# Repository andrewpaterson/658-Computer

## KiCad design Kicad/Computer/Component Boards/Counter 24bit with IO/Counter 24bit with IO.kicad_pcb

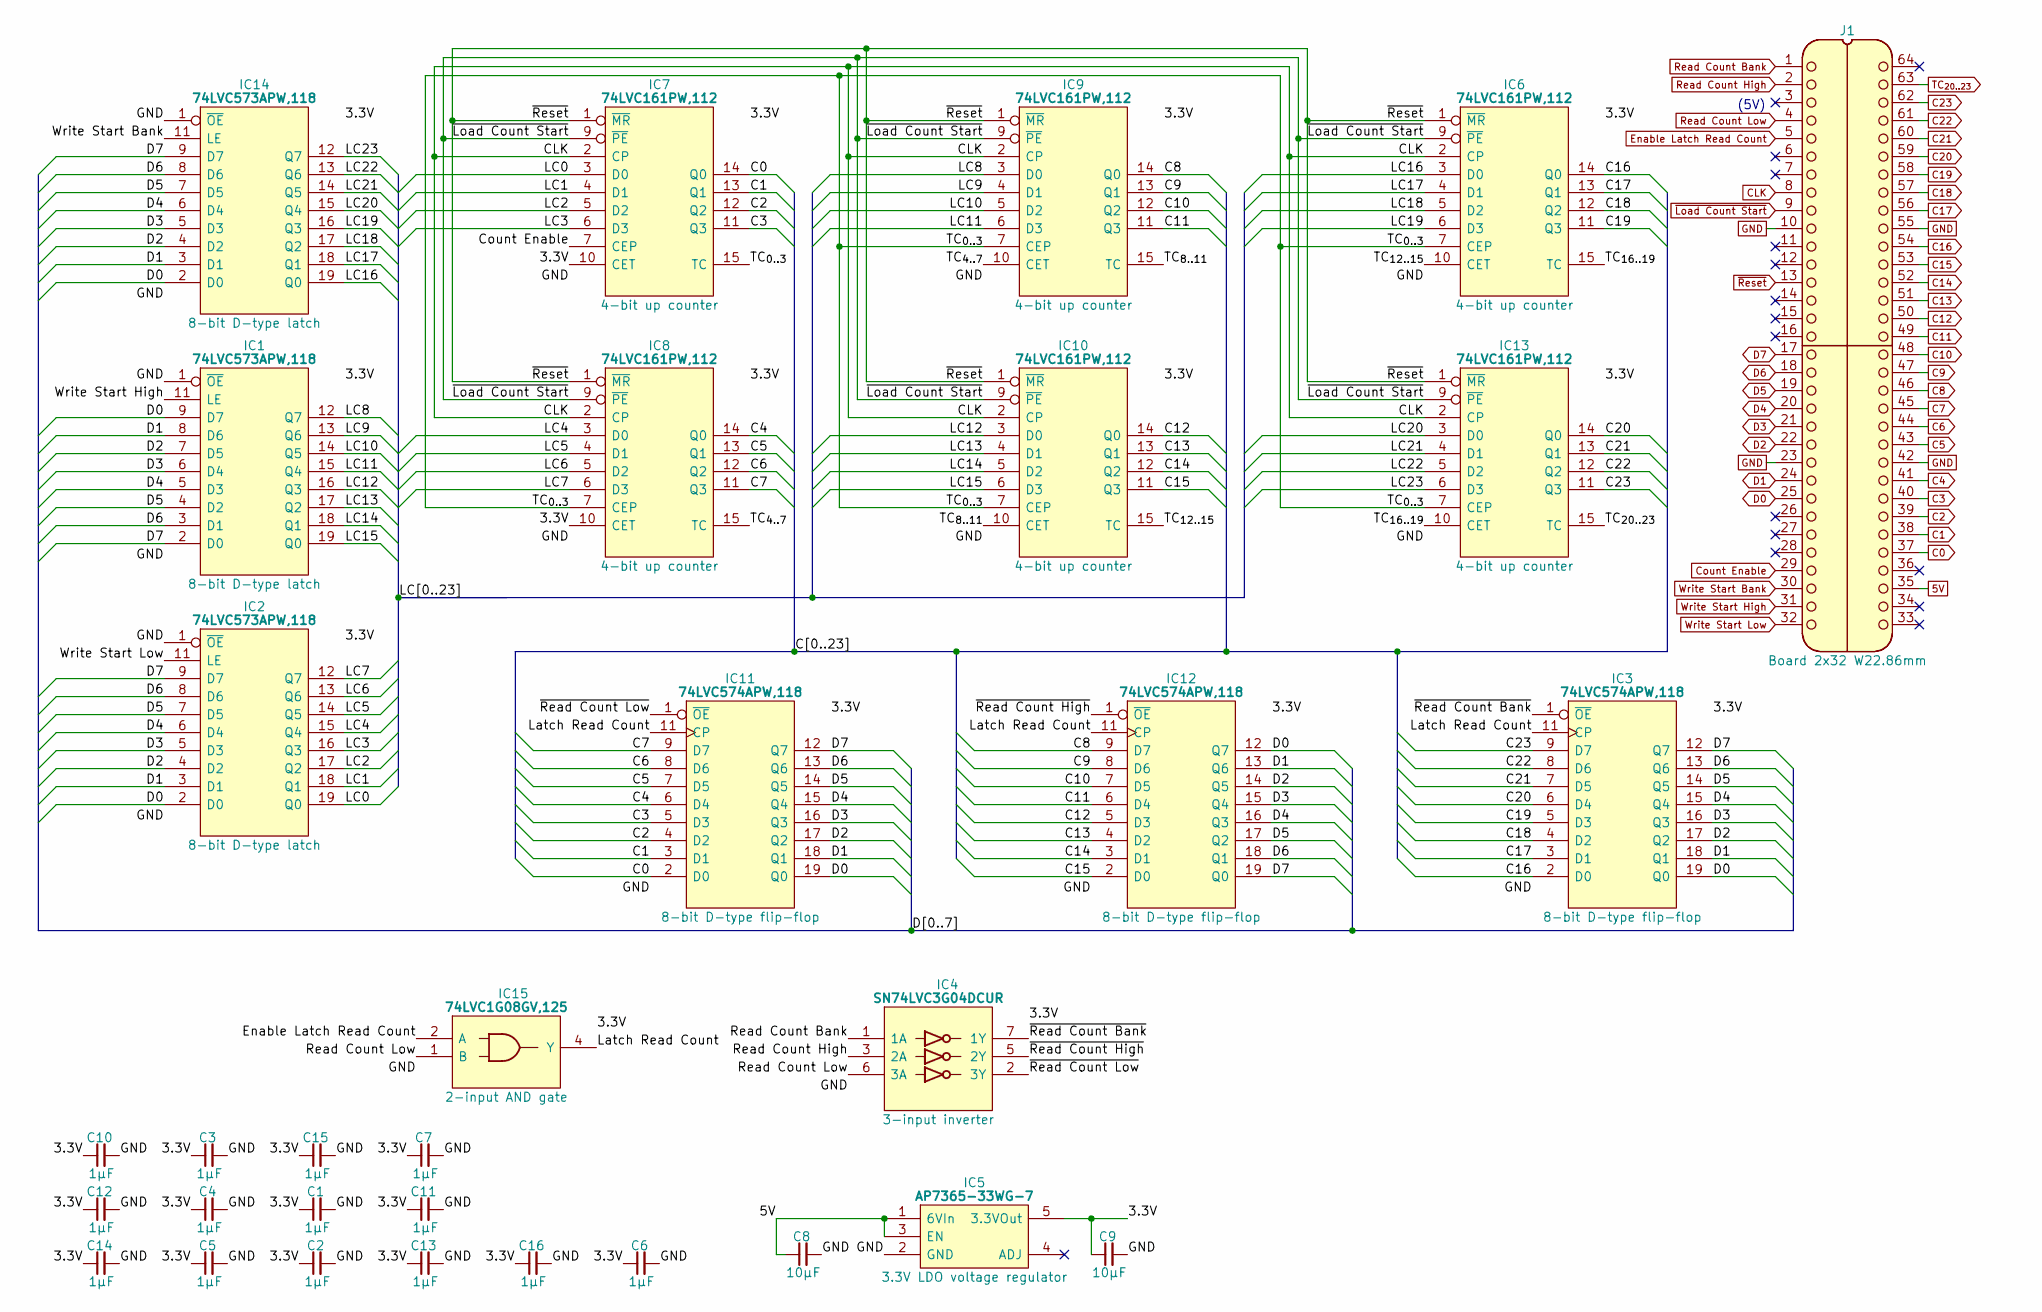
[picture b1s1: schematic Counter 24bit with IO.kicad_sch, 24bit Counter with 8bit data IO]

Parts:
C1, C2, C3, C4, C5, C6, C7, C10, C11, C12, C13, C14, C15, C16: 1μF; C_0805
C8, C9: 10µF; C_0805
IC1, IC2, IC14: 74LVC573APW,118; SOP65P640X110-20N; Mouser Part Number 771-74LVC573APW-T
IC3, IC11, IC12: 74LVC574APW,118; SOP65P640X110-20N; Manufacturer_Part_Number 74LVC574APW,118; Mouser Part Number 771-74LVC574APW-T
IC4: SN74LVC3G04DCUR; SOP50P310X90-8N; Manufacturer_Part_Number SN74LVC3G04DCUR; Mouser Part Number 595-SN74LVC3G04DCUR
IC5: AP7365-33WG-7; SOT95P285X130-5N; Manufacturer_Part_Number AP7365-33WG-7; Mouser Part Number 621-AP7365-33WG-7
IC6, IC7, IC8, IC9, IC10, IC13: 74LVC161PW,112; SOP65P640X110-16N; Mouser Part Number 771-LVC161PW112
IC15: 74LVC1G08GV,125; SOT95P275X110-5N; Manufacturer_Part_Number 74LVC1G08GV,125; Mouser Part Number 771-74LVC1G08GV
J1: Board 2x32 W22.86mm; DIP-64_Board_W22.86mm

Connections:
5V: C8.1, IC5.1 (6VIn), IC5.3 (EN), J1.35
/3.3V: C1.1, C2.1, C3.1, C4.1, C5.1, C6.1, C7.1, C9.1, C10.1, C11.1, C12.1, C13.1, C14.1, C15.1, C16.1, IC1.20 (3V), IC2.20 (3V), IC3.20 (3V), IC4.8 (3V), IC5.5 (3.3VOut), IC6.16 (3V), IC7.10 (CET), IC7.16 (3V), IC8.10 (CET), IC8.16 (3V), IC9.16 (3V), IC10.16 (3V), IC11.20 (3V), IC12.20 (3V), IC13.16 (3V), IC14.20 (3V), IC15.5 (3V)
/LC0: IC2.19 (Q0), IC7.3 (D0)
/LC1: IC2.18 (Q1), IC7.4 (D1)
/LC2: IC2.17 (Q2), IC7.5 (D2)
/LC3: IC2.16 (Q3), IC7.6 (D3)
/LC4: IC2.15 (Q4), IC8.3 (D0)
/LC5: IC2.14 (Q5), IC8.4 (D1)
/LC6: IC2.13 (Q6), IC8.5 (D2)
/LC7: IC2.12 (Q7), IC8.6 (D3)
/LC8: IC1.12 (Q7), IC9.3 (D0)
/LC9: IC1.13 (Q6), IC9.4 (D1)
/LC10: IC1.14 (Q5), IC9.5 (D2)
/LC11: IC1.15 (Q4), IC9.6 (D3)
/LC12: IC1.16 (Q3), IC10.3 (D0)
/LC13: IC1.17 (Q2), IC10.4 (D1)
/LC14: IC1.18 (Q1), IC10.5 (D2)
/LC15: IC1.19 (Q0), IC10.6 (D3)
/LC16: IC6.3 (D0), IC14.19 (Q0)
/LC17: IC6.4 (D1), IC14.18 (Q1)
/LC18: IC6.5 (D2), IC14.17 (Q2)
/LC19: IC6.6 (D3), IC14.16 (Q3)
/LC20: IC13.3 (D0), IC14.15 (Q4)
/LC21: IC13.4 (D1), IC14.14 (Q5)
/LC22: IC13.5 (D2), IC14.13 (Q6)
/LC23: IC13.6 (D3), IC14.12 (Q7)
/Latch Read Count: IC3.11 (CP), IC11.11 (CP), IC12.11 (CP), IC15.4 (Y)
/TC_{0..3}: IC6.7 (CEP), IC7.15 (TC), IC8.7 (CEP), IC9.7 (CEP), IC10.7 (CEP), IC13.7 (CEP)
/TC_{4..7}: IC8.15 (TC), IC9.10 (CET)
/TC_{8..11}: IC9.15 (TC), IC10.10 (CET)
/TC_{12..15}: IC6.10 (CET), IC10.15 (TC)
/TC_{16..19}: IC6.15 (TC), IC13.10 (CET)
/~Read Count Bank: IC3.1 (~OE), IC4.7 (1Y)
/~Read Count High: IC4.5 (2Y), IC12.1 (~OE)
/~Read Count Low: IC4.2 (3Y), IC11.1 (~OE)
C0: IC7.14 (Q0), IC11.2 (D0), J1.37
C1: IC7.13 (Q1), IC11.3 (D1), J1.38
C2: IC7.12 (Q2), IC11.4 (D2), J1.39
C3: IC7.11 (Q3), IC11.5 (D3), J1.40
C4: IC8.14 (Q0), IC11.6 (D4), J1.41
C5: IC8.13 (Q1), IC11.7 (D5), J1.43
C6: IC8.12 (Q2), IC11.8 (D6), J1.44
C7: IC8.11 (Q3), IC11.9 (D7), J1.45
C8: IC9.14 (Q0), IC12.9 (D7), J1.46
C9: IC9.13 (Q1), IC12.8 (D6), J1.47
C10: IC9.12 (Q2), IC12.7 (D5), J1.48
C11: IC9.11 (Q3), IC12.6 (D4), J1.49
C12: IC10.14 (Q0), IC12.5 (D3), J1.50
C13: IC10.13 (Q1), IC12.4 (D2), J1.51
C14: IC10.12 (Q2), IC12.3 (D1), J1.52
C15: IC10.11 (Q3), IC12.2 (D0), J1.53
C16: IC3.2 (D0), IC6.14 (Q0), J1.54
C17: IC3.3 (D1), IC6.13 (Q1), J1.56
C18: IC3.4 (D2), IC6.12 (Q2), J1.57
C19: IC3.5 (D3), IC6.11 (Q3), J1.58
C20: IC3.6 (D4), IC13.14 (Q0), J1.59
C21: IC3.7 (D5), IC13.13 (Q1), J1.60
C22: IC3.8 (D6), IC13.12 (Q2), J1.61
C23: IC3.9 (D7), IC13.11 (Q3), J1.62
CLK: IC6.2 (CP), IC7.2 (CP), IC8.2 (CP), IC9.2 (CP), IC10.2 (CP), IC13.2 (CP), J1.8
Count Enable: IC7.7 (CEP), J1.29
D0: IC1.9 (D7), IC2.2 (D0), IC3.19 (Q0), IC11.19 (Q0), IC12.12 (Q7), IC14.2 (D0), J1.25
D1: IC1.8 (D6), IC2.3 (D1), IC3.18 (Q1), IC11.18 (Q1), IC12.13 (Q6), IC14.3 (D1), J1.24
D2: IC1.7 (D5), IC2.4 (D2), IC3.17 (Q2), IC11.17 (Q2), IC12.14 (Q5), IC14.4 (D2), J1.22
D3: IC1.6 (D4), IC2.5 (D3), IC3.16 (Q3), IC11.16 (Q3), IC12.15 (Q4), IC14.5 (D3), J1.21
D4: IC1.5 (D3), IC2.6 (D4), IC3.15 (Q4), IC11.15 (Q4), IC12.16 (Q3), IC14.6 (D4), J1.20
D5: IC1.4 (D2), IC2.7 (D5), IC3.14 (Q5), IC11.14 (Q5), IC12.17 (Q2), IC14.7 (D5), J1.19
D6: IC1.3 (D1), IC2.8 (D6), IC3.13 (Q6), IC11.13 (Q6), IC12.18 (Q1), IC14.8 (D6), J1.18
D7: IC1.2 (D0), IC2.9 (D7), IC3.12 (Q7), IC11.12 (Q7), IC12.19 (Q0), IC14.9 (D7), J1.17
Enable Latch Read Count: IC15.2 (A), J1.5
GND: C1.2, C2.2, C3.2, C4.2, C5.2, C6.2, C7.2, C8.2, C9.2, C10.2, C11.2, C12.2, C13.2, C14.2, C15.2, C16.2, IC1.1 (~OE), IC1.10 (GND), IC2.1 (~OE), IC2.10 (GND), IC3.10 (GND), IC4.4 (GND), IC5.2 (GND), IC6.8 (GND), IC7.8 (GND), IC8.8 (GND), IC9.8 (GND), IC10.8 (GND), IC11.10 (GND), IC12.10 (GND), IC13.8 (GND), IC14.1 (~OE), IC14.10 (GND), IC15.3 (GND), J1.10, J1.23, J1.42, J1.55
Read Count Bank: IC4.1 (1A), J1.1
Read Count High: IC4.3 (2A), J1.2
Read Count Low: IC4.6 (3A), IC15.1 (B), J1.4
TC_{20..23}: IC13.15 (TC), J1.63
Write Start Bank: IC14.11 (LE), J1.30
Write Start High: IC1.11 (LE), J1.31
Write Start Low: IC2.11 (LE), J1.32
~Load Count Start: IC6.9 (~PE), IC7.9 (~PE), IC8.9 (~PE), IC9.9 (~PE), IC10.9 (~PE), IC13.9 (~PE), J1.9
~Reset: IC6.1 (~MR), IC7.1 (~MR), IC8.1 (~MR), IC9.1 (~MR), IC10.1 (~MR), IC13.1 (~MR), J1.13

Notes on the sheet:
(5V)

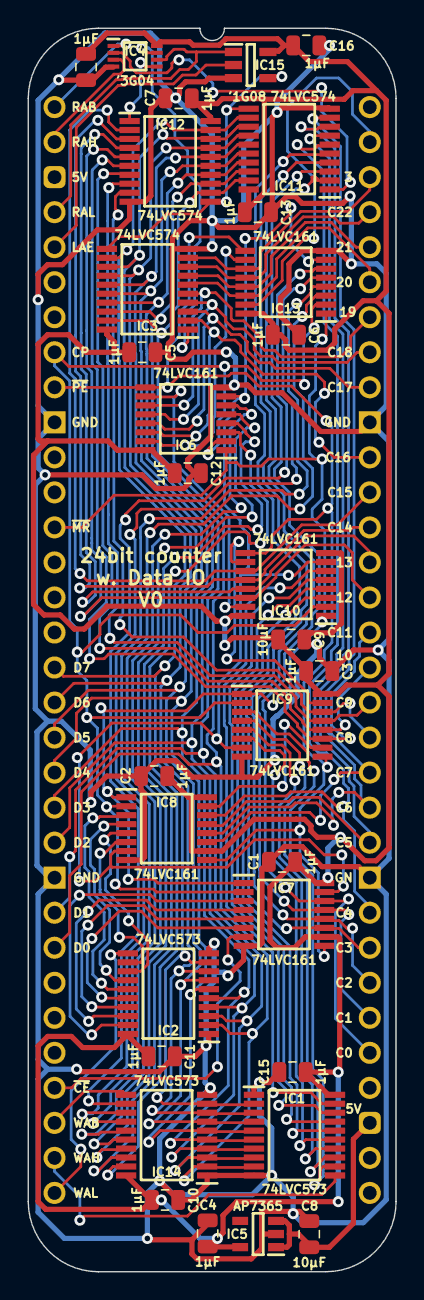
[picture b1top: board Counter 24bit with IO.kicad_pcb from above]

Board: 2 copper layers, 26.7 x 90.2 mm, 32 parts (0 on the bottom side), 80 nets.

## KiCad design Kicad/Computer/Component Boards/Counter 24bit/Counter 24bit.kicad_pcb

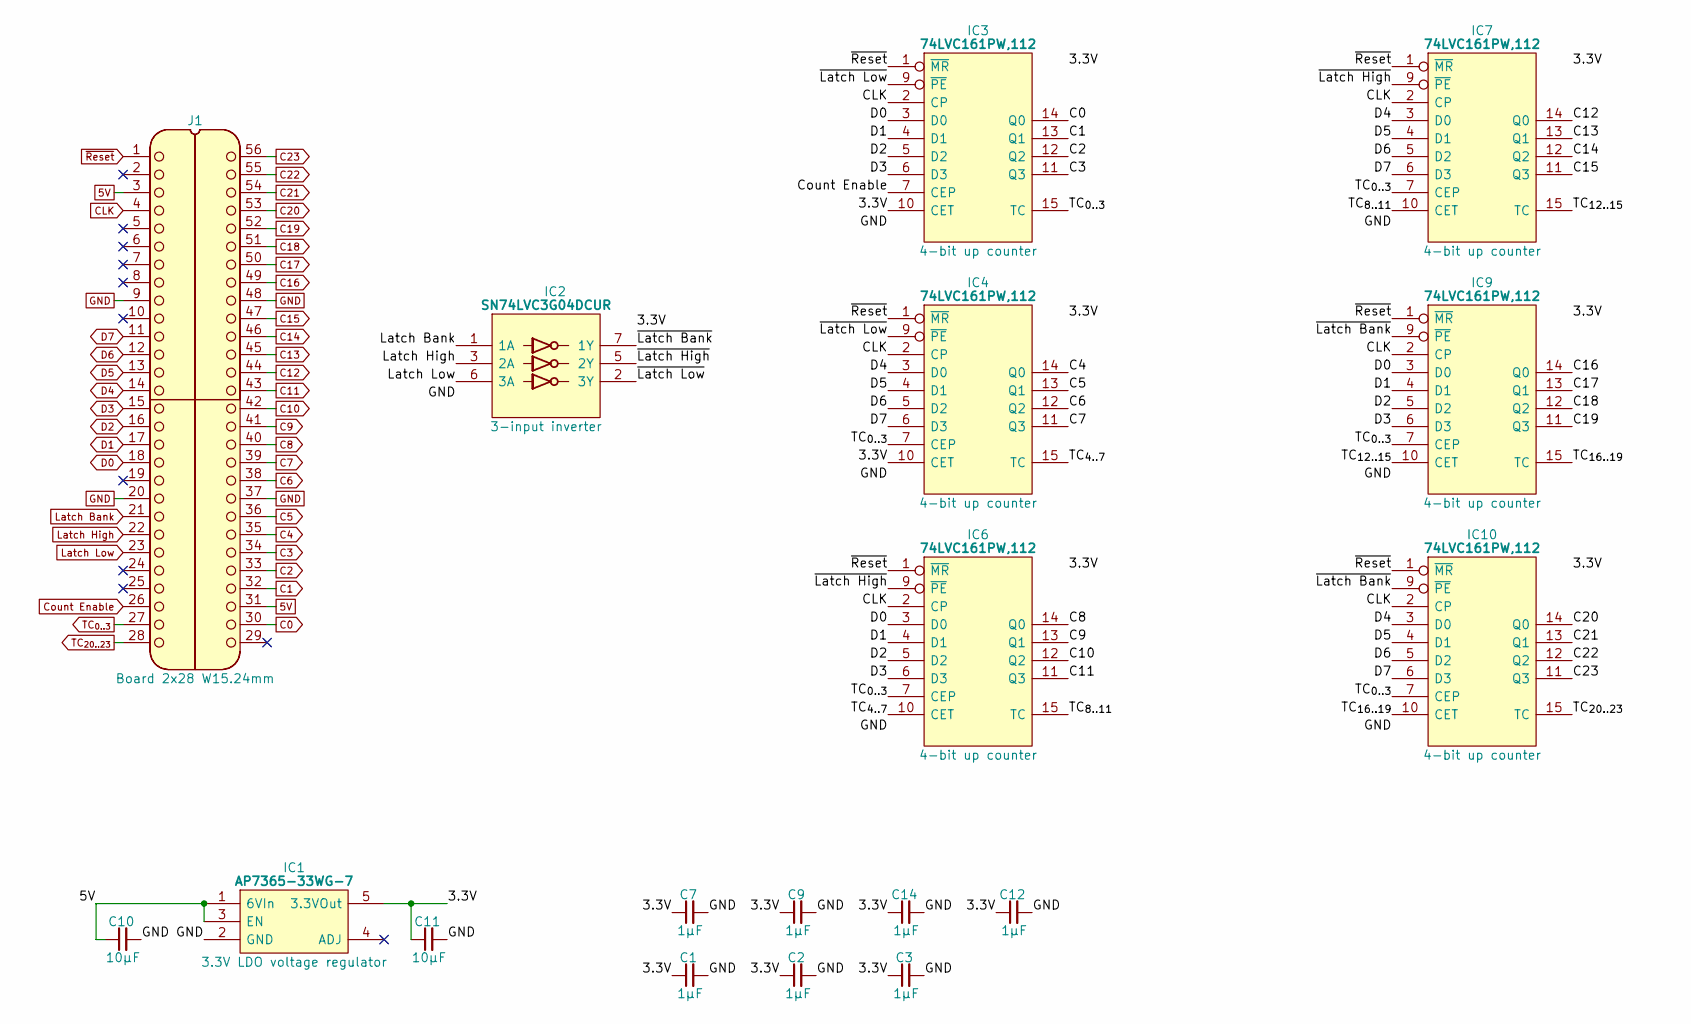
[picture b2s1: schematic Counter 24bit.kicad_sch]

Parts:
C1, C2, C3, C7, C9, C12, C14: 1μF; C_0805
C10, C11: 10µF; C_0805
IC1: AP7365-33WG-7; SOT95P285X130-5N; Manufacturer_Part_Number AP7365-33WG-7; Mouser Part Number 621-AP7365-33WG-7
IC2: SN74LVC3G04DCUR; SOP50P310X90-8N; Manufacturer_Part_Number SN74LVC3G04DCUR; Mouser Part Number 595-SN74LVC3G04DCUR
IC3, IC4, IC6, IC7, IC9, IC10: 74LVC161PW,112; SOP65P640X110-16N; Mouser Part Number 771-LVC161PW112
J1: Board 2x28 W15.24mm; DIP-56_Board_W15.24mm

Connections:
5V: C10.1, IC1.1 (6VIn), IC1.3 (EN), J1.3, J1.31
/3.3V: C1.1, C2.1, C3.1, C7.1, C9.1, C11.1, C12.1, C14.1, IC1.5 (3.3VOut), IC2.8 (3V), IC3.10 (CET), IC3.16 (3V), IC4.10 (CET), IC4.16 (3V), IC6.16 (3V), IC7.16 (3V), IC9.16 (3V), IC10.16 (3V)
/TC_{4..7}: IC4.15 (TC), IC6.10 (CET)
/TC_{8..11}: IC6.15 (TC), IC7.10 (CET)
/TC_{12..15}: IC7.15 (TC), IC9.10 (CET)
/TC_{16..19}: IC9.15 (TC), IC10.10 (CET)
/~Latch Bank: IC2.7 (1Y), IC9.9 (~PE), IC10.9 (~PE)
/~Latch High: IC2.5 (2Y), IC6.9 (~PE), IC7.9 (~PE)
/~Latch Low: IC2.2 (3Y), IC3.9 (~PE), IC4.9 (~PE)
C0: IC3.14 (Q0), J1.30
C1: IC3.13 (Q1), J1.32
C2: IC3.12 (Q2), J1.33
C3: IC3.11 (Q3), J1.34
C4: IC4.14 (Q0), J1.35
C5: IC4.13 (Q1), J1.36
C6: IC4.12 (Q2), J1.38
C7: IC4.11 (Q3), J1.39
C8: IC6.14 (Q0), J1.40
C9: IC6.13 (Q1), J1.41
C10: IC6.12 (Q2), J1.42
C11: IC6.11 (Q3), J1.43
C12: IC7.14 (Q0), J1.44
C13: IC7.13 (Q1), J1.45
C14: IC7.12 (Q2), J1.46
C15: IC7.11 (Q3), J1.47
C16: IC9.14 (Q0), J1.49
C17: IC9.13 (Q1), J1.50
C18: IC9.12 (Q2), J1.51
C19: IC9.11 (Q3), J1.52
C20: IC10.14 (Q0), J1.53
C21: IC10.13 (Q1), J1.54
C22: IC10.12 (Q2), J1.55
C23: IC10.11 (Q3), J1.56
CLK: IC3.2 (CP), IC4.2 (CP), IC6.2 (CP), IC7.2 (CP), IC9.2 (CP), IC10.2 (CP), J1.4
Count Enable: IC3.7 (CEP), J1.26
D0: IC3.3 (D0), IC6.3 (D0), IC9.3 (D0), J1.18
D1: IC3.4 (D1), IC6.4 (D1), IC9.4 (D1), J1.17
D2: IC3.5 (D2), IC6.5 (D2), IC9.5 (D2), J1.16
D3: IC3.6 (D3), IC6.6 (D3), IC9.6 (D3), J1.15
D4: IC4.3 (D0), IC7.3 (D0), IC10.3 (D0), J1.14
D5: IC4.4 (D1), IC7.4 (D1), IC10.4 (D1), J1.13
D6: IC4.5 (D2), IC7.5 (D2), IC10.5 (D2), J1.12
D7: IC4.6 (D3), IC7.6 (D3), IC10.6 (D3), J1.11
GND: C1.2, C2.2, C3.2, C7.2, C9.2, C10.2, C11.2, C12.2, C14.2, IC1.2 (GND), IC2.4 (GND), IC3.8 (GND), IC4.8 (GND), IC6.8 (GND), IC7.8 (GND), IC9.8 (GND), IC10.8 (GND), J1.9, J1.20, J1.37, J1.48
Latch Bank: IC2.1 (1A), J1.21
Latch High: IC2.3 (2A), J1.22
Latch Low: IC2.6 (3A), J1.23
TC_{0..3}: IC3.15 (TC), IC4.7 (CEP), IC6.7 (CEP), IC7.7 (CEP), IC9.7 (CEP), IC10.7 (CEP), J1.27
TC_{20..23}: IC10.15 (TC), J1.28
~Reset: IC3.1 (~MR), IC4.1 (~MR), IC6.1 (~MR), IC7.1 (~MR), IC9.1 (~MR), IC10.1 (~MR), J1.1

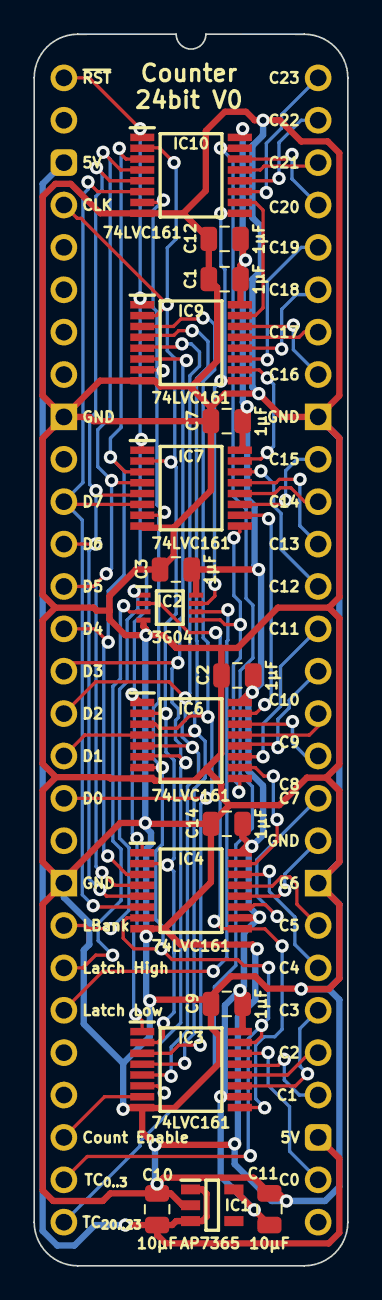
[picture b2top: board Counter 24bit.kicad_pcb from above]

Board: 2 copper layers, 18.8 x 73.8 mm, 18 parts (0 on the bottom side), 50 nets.

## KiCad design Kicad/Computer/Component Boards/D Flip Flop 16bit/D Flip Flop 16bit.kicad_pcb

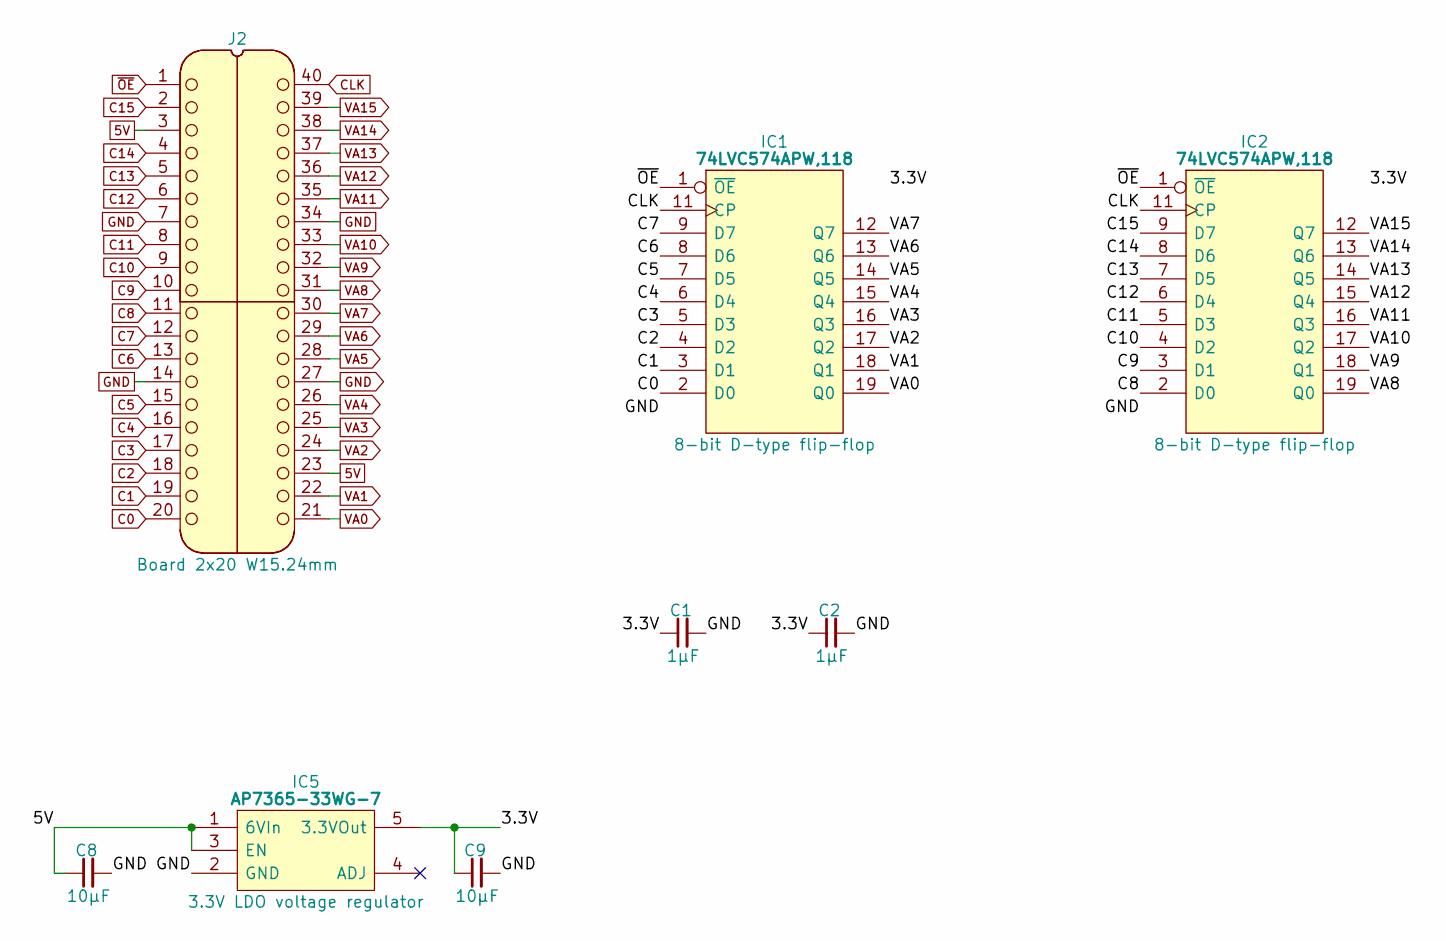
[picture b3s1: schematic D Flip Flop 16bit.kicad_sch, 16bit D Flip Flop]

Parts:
C1, C2: 1μF; C_0805
C8, C9: 10µF; C_0805
IC1, IC2: 74LVC574APW,118; SOP65P640X110-20N; Manufacturer_Part_Number 74LVC574APW,118; Mouser Part Number 771-74LVC574APW-T
IC5: AP7365-33WG-7; SOT95P285X130-5N; Manufacturer_Part_Number AP7365-33WG-7; Mouser Part Number 621-AP7365-33WG-7
J2: Board 2x20 W15.24mm; DIP-40_Board_W15.24mm

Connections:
5V: C8.1, IC5.1 (6VIn), IC5.3 (EN), J2.3, J2.23
/3.3V: C1.1, C2.1, C9.1, IC1.20 (3V), IC2.20 (3V), IC5.5 (3.3VOut)
C0: IC1.2 (D0), J2.20
C1: IC1.3 (D1), J2.19
C2: IC1.4 (D2), J2.18
C3: IC1.5 (D3), J2.17
C4: IC1.6 (D4), J2.16
C5: IC1.7 (D5), J2.15
C6: IC1.8 (D6), J2.13
C7: IC1.9 (D7), J2.12
C8: IC2.2 (D0), J2.11
C9: IC2.3 (D1), J2.10
C10: IC2.4 (D2), J2.9
C11: IC2.5 (D3), J2.8
C12: IC2.6 (D4), J2.6
C13: IC2.7 (D5), J2.5
C14: IC2.8 (D6), J2.4
C15: IC2.9 (D7), J2.2
CLK: IC1.11 (CP), IC2.11 (CP), J2.40
GND: C1.2, C2.2, C8.2, C9.2, IC1.10 (GND), IC2.10 (GND), IC5.2 (GND), J2.7, J2.14, J2.27, J2.34
VA0: IC1.19 (Q0), J2.21
VA1: IC1.18 (Q1), J2.22
VA2: IC1.17 (Q2), J2.24
VA3: IC1.16 (Q3), J2.25
VA4: IC1.15 (Q4), J2.26
VA5: IC1.14 (Q5), J2.28
VA6: IC1.13 (Q6), J2.29
VA7: IC1.12 (Q7), J2.30
VA8: IC2.19 (Q0), J2.31
VA9: IC2.18 (Q1), J2.32
VA10: IC2.17 (Q2), J2.33
VA11: IC2.16 (Q3), J2.35
VA12: IC2.15 (Q4), J2.36
VA13: IC2.14 (Q5), J2.37
VA14: IC2.13 (Q6), J2.38
VA15: IC2.12 (Q7), J2.39
~OE: IC1.1 (~OE), IC2.1 (~OE), J2.1

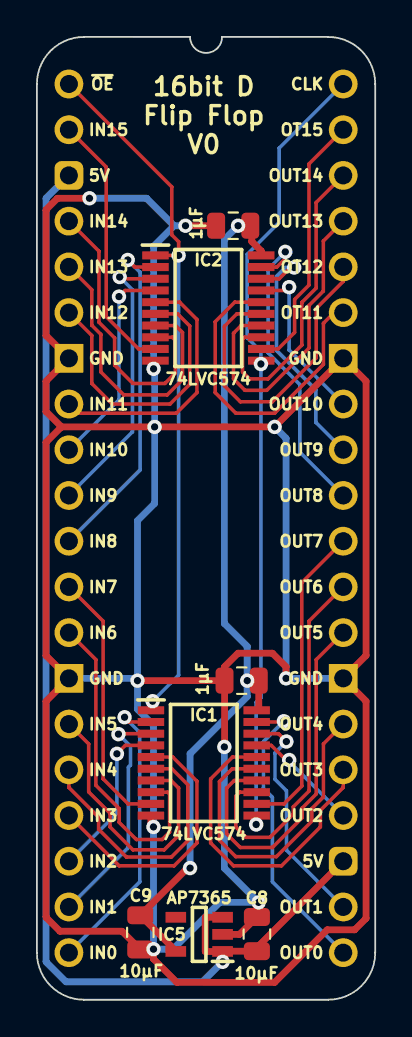
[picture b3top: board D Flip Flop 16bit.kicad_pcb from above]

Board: 2 copper layers, 18.8 x 53.5 mm, 8 parts (0 on the bottom side), 37 nets.

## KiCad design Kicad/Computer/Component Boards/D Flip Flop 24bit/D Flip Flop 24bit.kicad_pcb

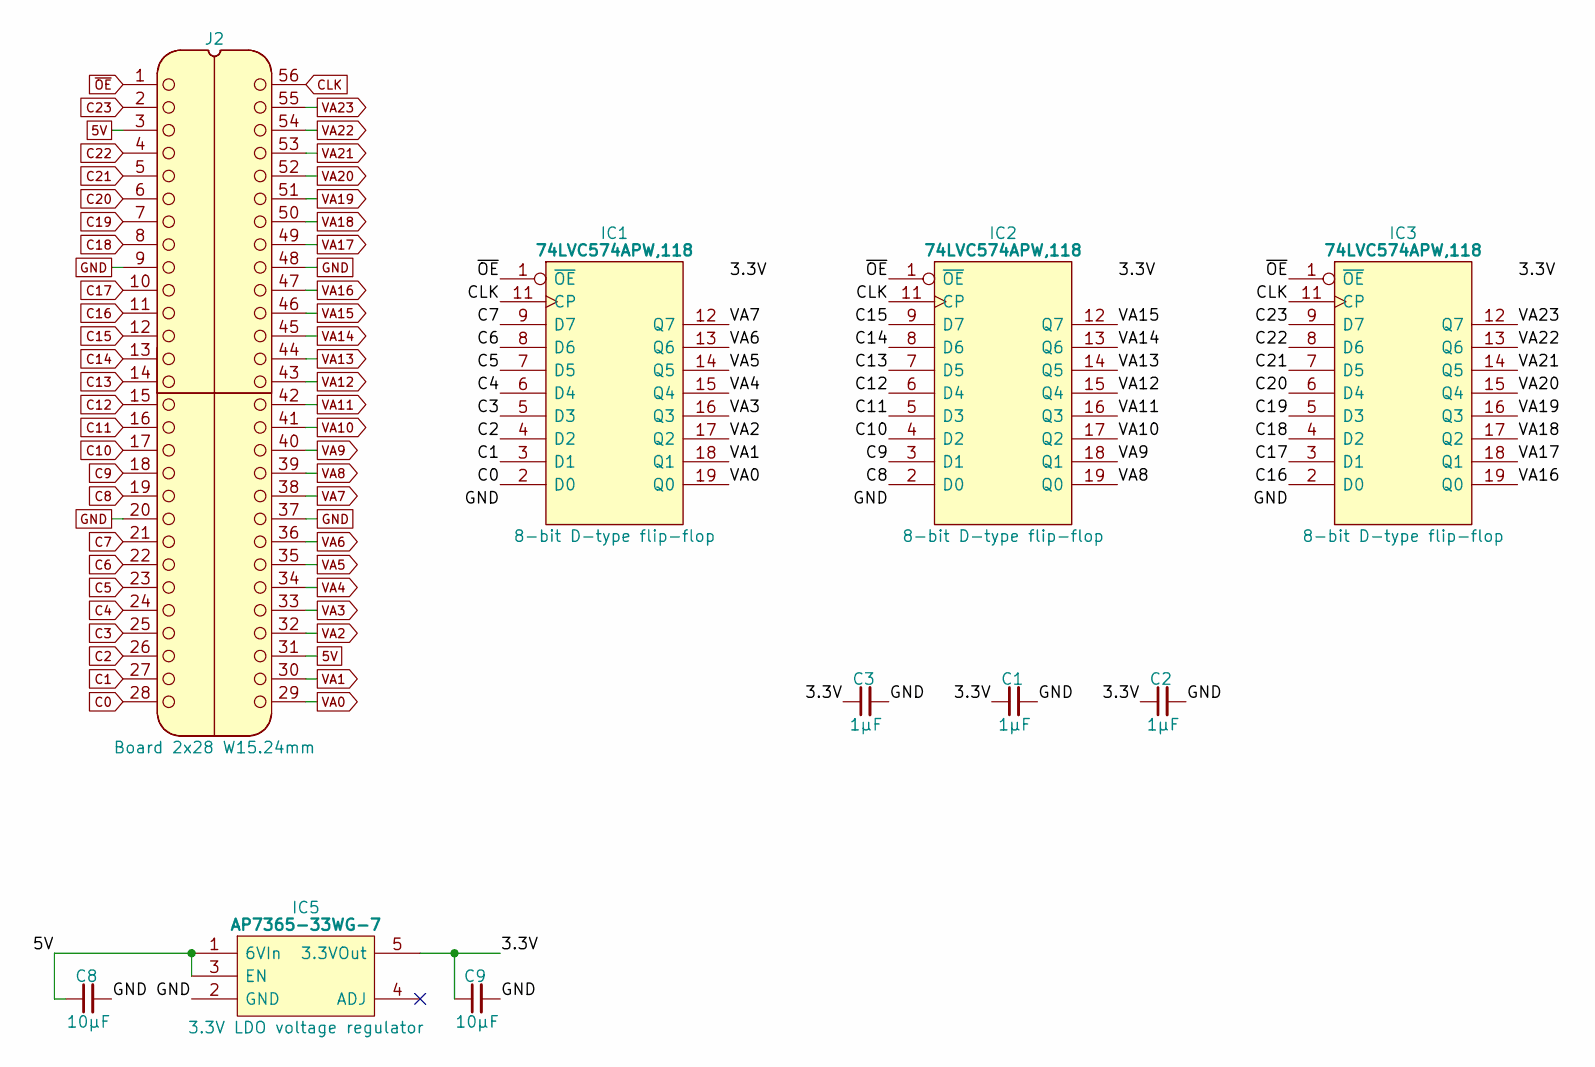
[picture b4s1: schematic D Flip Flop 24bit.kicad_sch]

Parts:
C1, C2, C3: 1μF; C_0805
C8, C9: 10µF; C_0805
IC1, IC2, IC3: 74LVC574APW,118; SOP65P640X110-20N; Manufacturer_Part_Number 74LVC574APW,118; Mouser Part Number 771-74LVC574APW-T
IC5: AP7365-33WG-7; SOT95P285X130-5N; Manufacturer_Part_Number AP7365-33WG-7; Mouser Part Number 621-AP7365-33WG-7
J2: Board 2x28 W15.24mm; DIP-56_Board_W15.24mm

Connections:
5V: C8.1, IC5.1 (6VIn), IC5.3 (EN), J2.3, J2.31
/3.3V: C1.1, C2.1, C3.1, C9.1, IC1.20 (3V), IC2.20 (3V), IC3.20 (3V), IC5.5 (3.3VOut)
C0: IC1.2 (D0), J2.28
C1: IC1.3 (D1), J2.27
C2: IC1.4 (D2), J2.26
C3: IC1.5 (D3), J2.25
C4: IC1.6 (D4), J2.24
C5: IC1.7 (D5), J2.23
C6: IC1.8 (D6), J2.22
C7: IC1.9 (D7), J2.21
C8: IC2.2 (D0), J2.19
C9: IC2.3 (D1), J2.18
C10: IC2.4 (D2), J2.17
C11: IC2.5 (D3), J2.16
C12: IC2.6 (D4), J2.15
C13: IC2.7 (D5), J2.14
C14: IC2.8 (D6), J2.13
C15: IC2.9 (D7), J2.12
C16: IC3.2 (D0), J2.11
C17: IC3.3 (D1), J2.10
C18: IC3.4 (D2), J2.8
C19: IC3.5 (D3), J2.7
C20: IC3.6 (D4), J2.6
C21: IC3.7 (D5), J2.5
C22: IC3.8 (D6), J2.4
C23: IC3.9 (D7), J2.2
CLK: IC1.11 (CP), IC2.11 (CP), IC3.11 (CP), J2.56
GND: C1.2, C2.2, C3.2, C8.2, C9.2, IC1.10 (GND), IC2.10 (GND), IC3.10 (GND), IC5.2 (GND), J2.9, J2.20, J2.37, J2.48
VA0: IC1.19 (Q0), J2.29
VA1: IC1.18 (Q1), J2.30
VA2: IC1.17 (Q2), J2.32
VA3: IC1.16 (Q3), J2.33
VA4: IC1.15 (Q4), J2.34
VA5: IC1.14 (Q5), J2.35
VA6: IC1.13 (Q6), J2.36
VA7: IC1.12 (Q7), J2.38
VA8: IC2.19 (Q0), J2.39
VA9: IC2.18 (Q1), J2.40
VA10: IC2.17 (Q2), J2.41
VA11: IC2.16 (Q3), J2.42
VA12: IC2.15 (Q4), J2.43
VA13: IC2.14 (Q5), J2.44
VA14: IC2.13 (Q6), J2.45
VA15: IC2.12 (Q7), J2.46
VA16: IC3.19 (Q0), J2.47
VA17: IC3.18 (Q1), J2.49
VA18: IC3.17 (Q2), J2.50
VA19: IC3.16 (Q3), J2.51
VA20: IC3.15 (Q4), J2.52
VA21: IC3.14 (Q5), J2.53
VA22: IC3.13 (Q6), J2.54
VA23: IC3.12 (Q7), J2.55
~OE: IC1.1 (~OE), IC2.1 (~OE), IC3.1 (~OE), J2.1

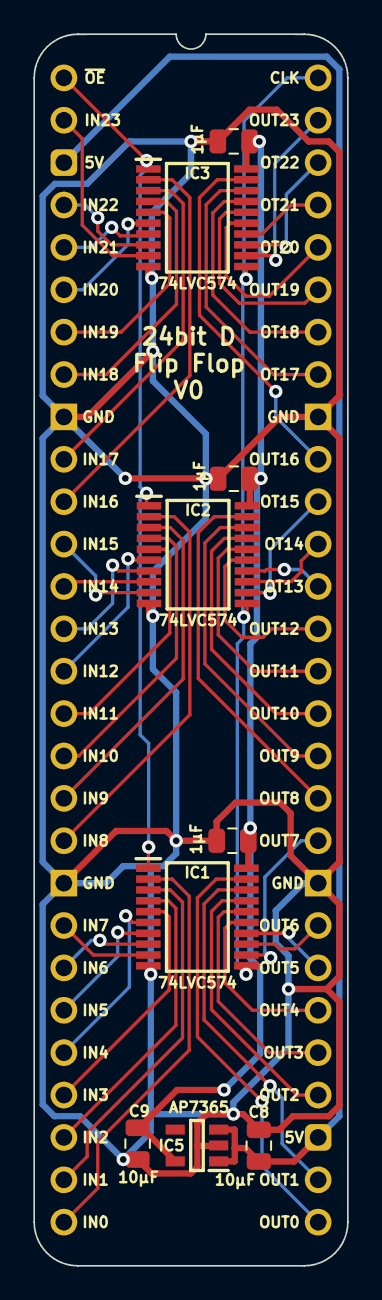
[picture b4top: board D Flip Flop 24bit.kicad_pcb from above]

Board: 2 copper layers, 18.8 x 73.8 mm, 10 parts (0 on the bottom side), 53 nets.

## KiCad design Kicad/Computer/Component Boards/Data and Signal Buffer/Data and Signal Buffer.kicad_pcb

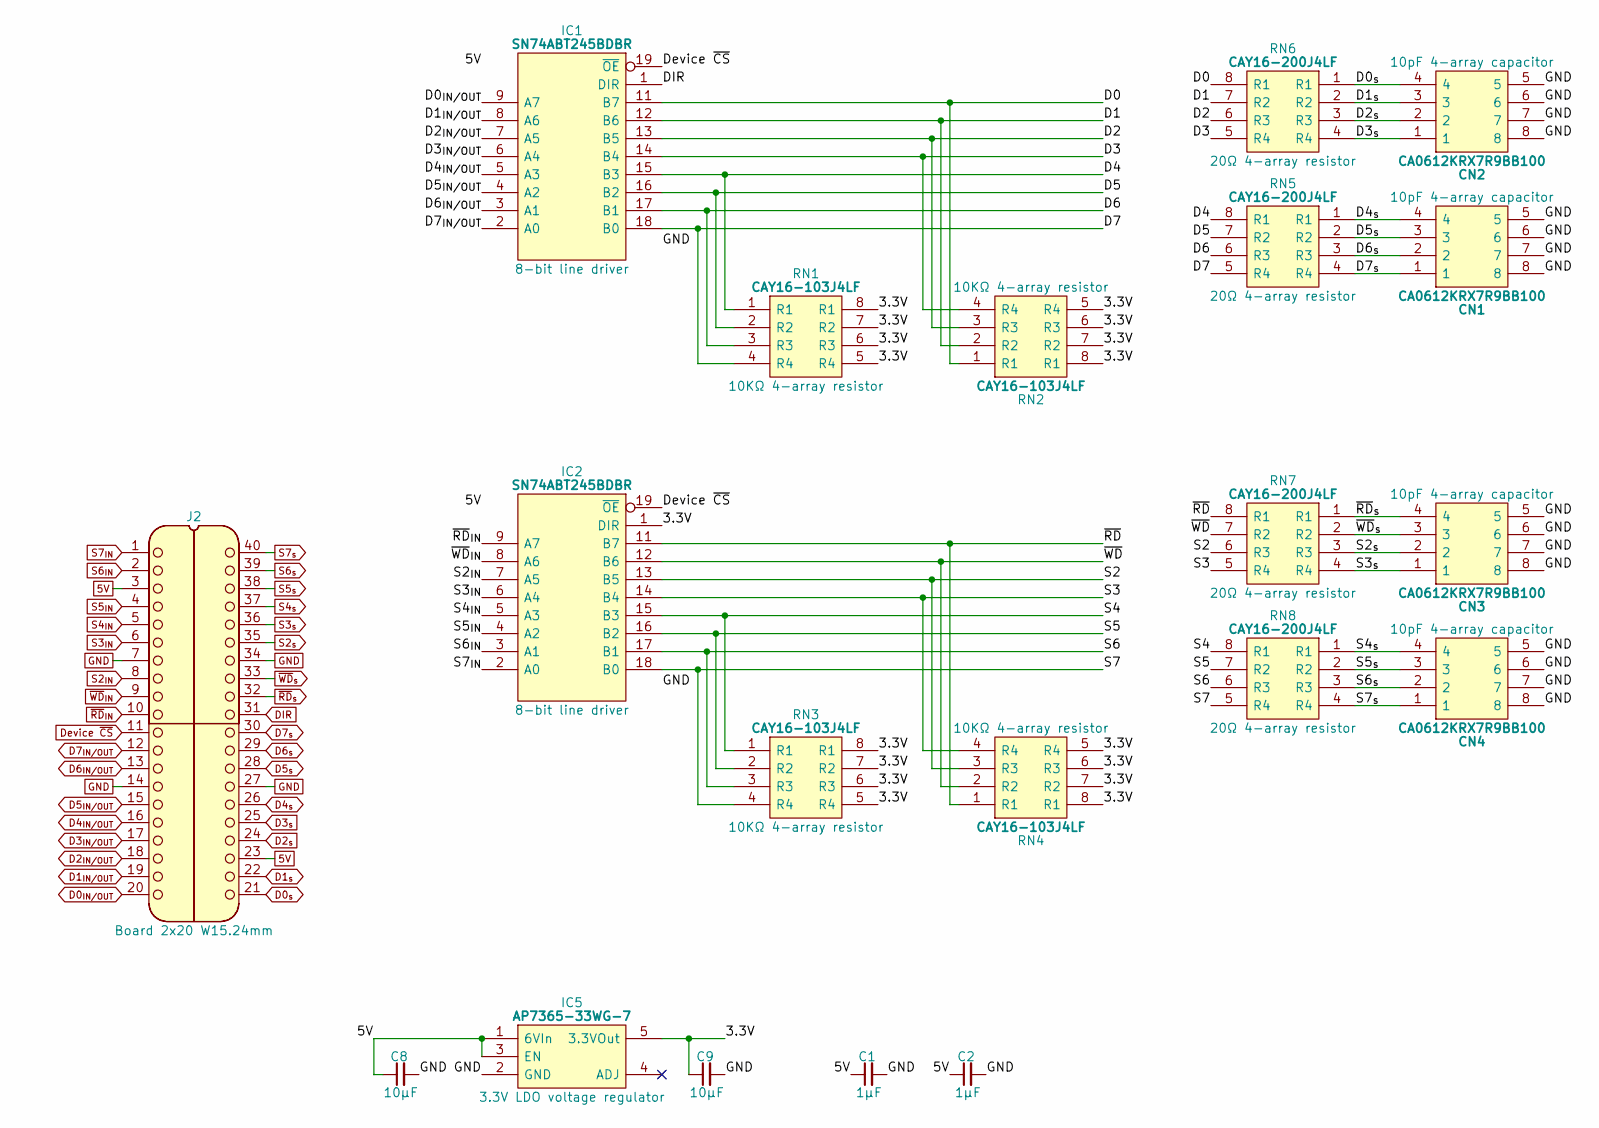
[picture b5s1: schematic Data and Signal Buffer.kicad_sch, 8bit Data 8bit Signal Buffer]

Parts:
C1, C2: 1μF; C_0805
C8, C9: 10µF; C_0805
CN1, CN2, CN3, CN4: CA0612KRX7R9BB100; Manufacturer_Part_Number CA0612KRX7R9BB102; Mouser Part Number 603-CA612KRX7R9BB102
IC1, IC2: SN74ABT245BDBR; SOP65P780X200-20N; Manufacturer_Part_Number SN74ABT245BDBR; Mouser Part Number 595-SN74ABT245BDBR
IC5: AP7365-33WG-7; SOT95P285X130-5N; Manufacturer_Part_Number AP7365-33WG-7; Mouser Part Number 621-AP7365-33WG-7
J2: Board 2x20 W15.24mm; DIP-40_Board_W15.24mm
RN1, RN2, RN3, RN4: CAY16-103J4LF; CAY16-J4; Manufacturer_Part_Number CAY16-103J4LF; Mouser Part Number 652-CAY16-103J4LF
RN5, RN6, RN7, RN8: CAY16-200J4LF; CAY16-F4; Manufacturer_Part_Number CAY16-331J4LF; Mouser Part Number 652-CAY16-331J4LF

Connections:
5V: C1.1, C2.1, C8.1, IC1.20 (5V), IC2.20 (5V), IC5.1 (6VIn), IC5.3 (EN), J2.3, J2.23
/3.3V: C9.1, IC2.1 (DIR), IC5.5 (3.3VOut), RN1.5 (R4), RN1.6 (R3), RN1.7 (R2), RN1.8 (R1), RN2.5 (R4), RN2.6 (R3), RN2.7 (R2), RN2.8 (R1), RN3.5 (R4), RN3.6 (R3), RN3.7 (R2), RN3.8 (R1), RN4.5 (R4), RN4.6 (R3), RN4.7 (R2), RN4.8 (R1)
/D0: IC1.11 (B7), RN2.1 (R1), RN6.8 (R1)
/D1: IC1.12 (B6), RN2.2 (R2), RN6.7 (R2)
/D2: IC1.13 (B5), RN2.3 (R3), RN6.6 (R3)
/D3: IC1.14 (B4), RN2.4 (R4), RN6.5 (R4)
/D4: IC1.15 (B3), RN1.1 (R1), RN5.8 (R1)
/D5: IC1.16 (B2), RN1.2 (R2), RN5.7 (R2)
/D6: IC1.17 (B1), RN1.3 (R3), RN5.6 (R3)
/D7: IC1.18 (B0), RN1.4 (R4), RN5.5 (R4)
/S2: IC2.13 (B5), RN4.3 (R3), RN7.6 (R3)
/S3: IC2.14 (B4), RN4.4 (R4), RN7.5 (R4)
/S4: IC2.15 (B3), RN3.1 (R1), RN8.8 (R1)
/S5: IC2.16 (B2), RN3.2 (R2), RN8.7 (R2)
/S6: IC2.17 (B1), RN3.3 (R3), RN8.6 (R3)
/S7: IC2.18 (B0), RN3.4 (R4), RN8.5 (R4)
/~RD: IC2.11 (B7), RN4.1 (R1), RN7.8 (R1)
/~WD: IC2.12 (B6), RN4.2 (R2), RN7.7 (R2)
D0_{IN/OUT}: IC1.9 (A7), J2.20
D0_{s}: CN2.4, J2.21, RN6.1 (R1)
D1_{IN/OUT}: IC1.8 (A6), J2.19
D1_{s}: CN2.3, J2.22, RN6.2 (R2)
D2_{IN/OUT}: IC1.7 (A5), J2.18
D2_{s}: CN2.2, J2.24, RN6.3 (R3)
D3_{IN/OUT}: IC1.6 (A4), J2.17
D3_{s}: CN2.1, J2.25, RN6.4 (R4)
D4_{IN/OUT}: IC1.5 (A3), J2.16
D4_{s}: CN1.4, J2.26, RN5.1 (R1)
D5_{IN/OUT}: IC1.4 (A2), J2.15
D5_{s}: CN1.3, J2.28, RN5.2 (R2)
D6_{IN/OUT}: IC1.3 (A1), J2.13
D6_{s}: CN1.2, J2.29, RN5.3 (R3)
D7_{IN/OUT}: IC1.2 (A0), J2.12
D7_{s}: CN1.1, J2.30, RN5.4 (R4)
DIR: IC1.1 (DIR), J2.31
Device ~CS: IC1.19 (~OE), IC2.19 (~OE), J2.11
GND: C1.2, C2.2, C8.2, C9.2, CN1.5, CN1.6, CN1.7, CN1.8, CN2.5, CN2.6, CN2.7, CN2.8, CN3.5, CN3.6, CN3.7, CN3.8, CN4.5, CN4.6, CN4.7, CN4.8, IC1.10 (GND), IC2.10 (GND), IC5.2 (GND), J2.7, J2.14, J2.27, J2.34
S2_{IN}: IC2.7 (A5), J2.8
S2_{s}: CN3.2, J2.35, RN7.3 (R3)
S3_{IN}: IC2.6 (A4), J2.6
S3_{s}: CN3.1, J2.36, RN7.4 (R4)
S4_{IN}: IC2.5 (A3), J2.5
S4_{s}: CN4.4, J2.37, RN8.1 (R1)
S5_{IN}: IC2.4 (A2), J2.4
S5_{s}: CN4.3, J2.38, RN8.2 (R2)
S6_{IN}: IC2.3 (A1), J2.2
S6_{s}: CN4.2, J2.39, RN8.3 (R3)
S7_{IN}: IC2.2 (A0), J2.1
S7_{s}: CN4.1, J2.40, RN8.4 (R4)
~RD_{IN}: IC2.9 (A7), J2.10
~RD_{s}: CN3.4, J2.32, RN7.1 (R1)
~WD_{IN}: IC2.8 (A6), J2.9
~WD_{s}: CN3.3, J2.33, RN7.2 (R2)

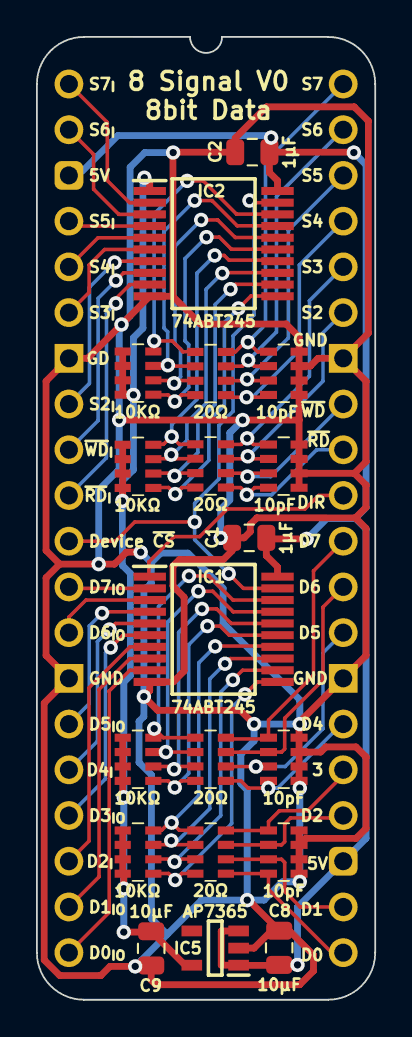
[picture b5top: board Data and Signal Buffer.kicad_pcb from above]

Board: 2 copper layers, 18.8 x 53.5 mm, 20 parts (0 on the bottom side), 53 nets.
